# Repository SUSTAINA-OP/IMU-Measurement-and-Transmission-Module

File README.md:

<html lang="en">

<head>
    <meta charset="uft-8">
    <meta name="author" content="Masato Kubotera">
    <meta name="description" content="">
</head>

<body>
    <p><strong>This product is currently under development!</strong></p>
    <h1>IMU Measurement and Transmission Module</h1>
        <p>
            This product is a module enabling the <a href="https://github.com/SUSTAINA-OP/ICM-42688-P-Module">SUSTAINA-OP/ICM-42688-P-Module</a> (IMU module) to be connected to a USB or RS-485 I/F through a microcontroller.<br><br>
            The <a href="/firmware">firmware</a> for this product to be written to the microcontroller is a modification of the following library.
            <ul>
                <li><a href="https://github.com/finani/ICM42688">finani/ICM42688</a></li>
            </ul>
            (The firmware of this product currently supports only USB I/F connection.)
        </p>
    <h2>Features Rev. 1</h2>
        <p>
            <table>
                <tr>
                    <th>Top Surface of PCB</th>
                    <th>Bottom Surface of PCB</th>
                    <th>Assembled Electronic Components</th>
                </tr>
                <tr>
                    <td></td>
                    <td></td>
                    <td></td>
                </tr>
            </table>
        </p>
    <h3>PCB</h3>
        <p>
            <ul>
                <li>87mm x 25mm PCB layout</li>
            </ul>
        </p>
    <h2>Development Environments</h2>
    <p>
        This product is designed with the following software.
            <ul>
                <li><a href="https://www.autodesk.com/products/eagle/overview">Autodesk Eagle 9.6.2</a></li>
                <li><a href="https://www.arduino.cc/en/software">Arduino IDE 1.8.19</a></li>
            </ul>
    </p>
    <h2>Repository Contents</h2>
        <p>
            <dl>
                <dt><a href="/images">\images</a></dt>
                <dd>PCB preview images and capture of design screen</dd>
                <dt><a href="/libraries">\libraries</a></dt>
                <dd>Libraries used in Autodesk Eagle design</dd>
                <dt><a href="/pcb_order">\pcb_order</a> </dt>
                <dd>Gerber data and documentation for ordering PCB</dd>
                <dt><a href="/firmware">\firmware</a> </dt>
                <dd>Sample firmware to be written to the microcontroller board</dd>
                <dt><a href="/schematic.pdf">schematic.pdf</a></dt>
                <dd>Circuit diagram of this product</dd>
                <dt>*.brd</dt>
                <dd>Board wiring design file by Autodesk Eagle</dd>
                <dt>*.sch</dt>
                <dd>Circuit diagram design file by Autodesk Eagle</dd>
                <dt><a href="/.gitignore">.gitignore</a></dt>
                <dd>A file that tells Git not to track a particular file</dd>
                <dt><a href="/LICENSE">LICENSE</a></dt>
                <dd>License to use this product</dd>
            </dl>
        </p>
    <h2>Documentation</h2>
    <h3>Documentation</h3>
        <p>
            The following design errors have been identified in Rev. 1 of this product.
            <ul>
              <li>TXDEN of UART/RS-485 conversion IC is not wired to the microcontroller board</li>
                When used with USB I/F, there is no problem, but when used with RS-485 I/F, solder a jumper wire between TXDEN and the microcontroller as shown in the figure below.<br>
                
            </ul>
        </p>
    <h2>References</h2>
        
    <h2>Contact</h2>
        <p>
            If you have any questions, please contact the designer of this product, Masato Kubodera, by <a href="mailto:masato.kubotera@sustaina-op.com">e-mail</a>.<br>
            E-mail: <a href="mailto:masato.kubotera@sustaina-op.com">masato.kubotera@sustaina-op.com</a>
        </p>
    <h2>License Information</h2>
        <p>
            This product is open source. Please review the <a href="/LICENSE">LICENSE</a> for license information.<br>
            <br>
            This product by Masato Kubotera is licensed under a <a href="http://creativecommons.org/licenses/by-nc-sa/4.0/">Creative Commons Attribution-NonCommercial-ShareAlike 4.0 International License</a>.
        </p>
</body>
</html>

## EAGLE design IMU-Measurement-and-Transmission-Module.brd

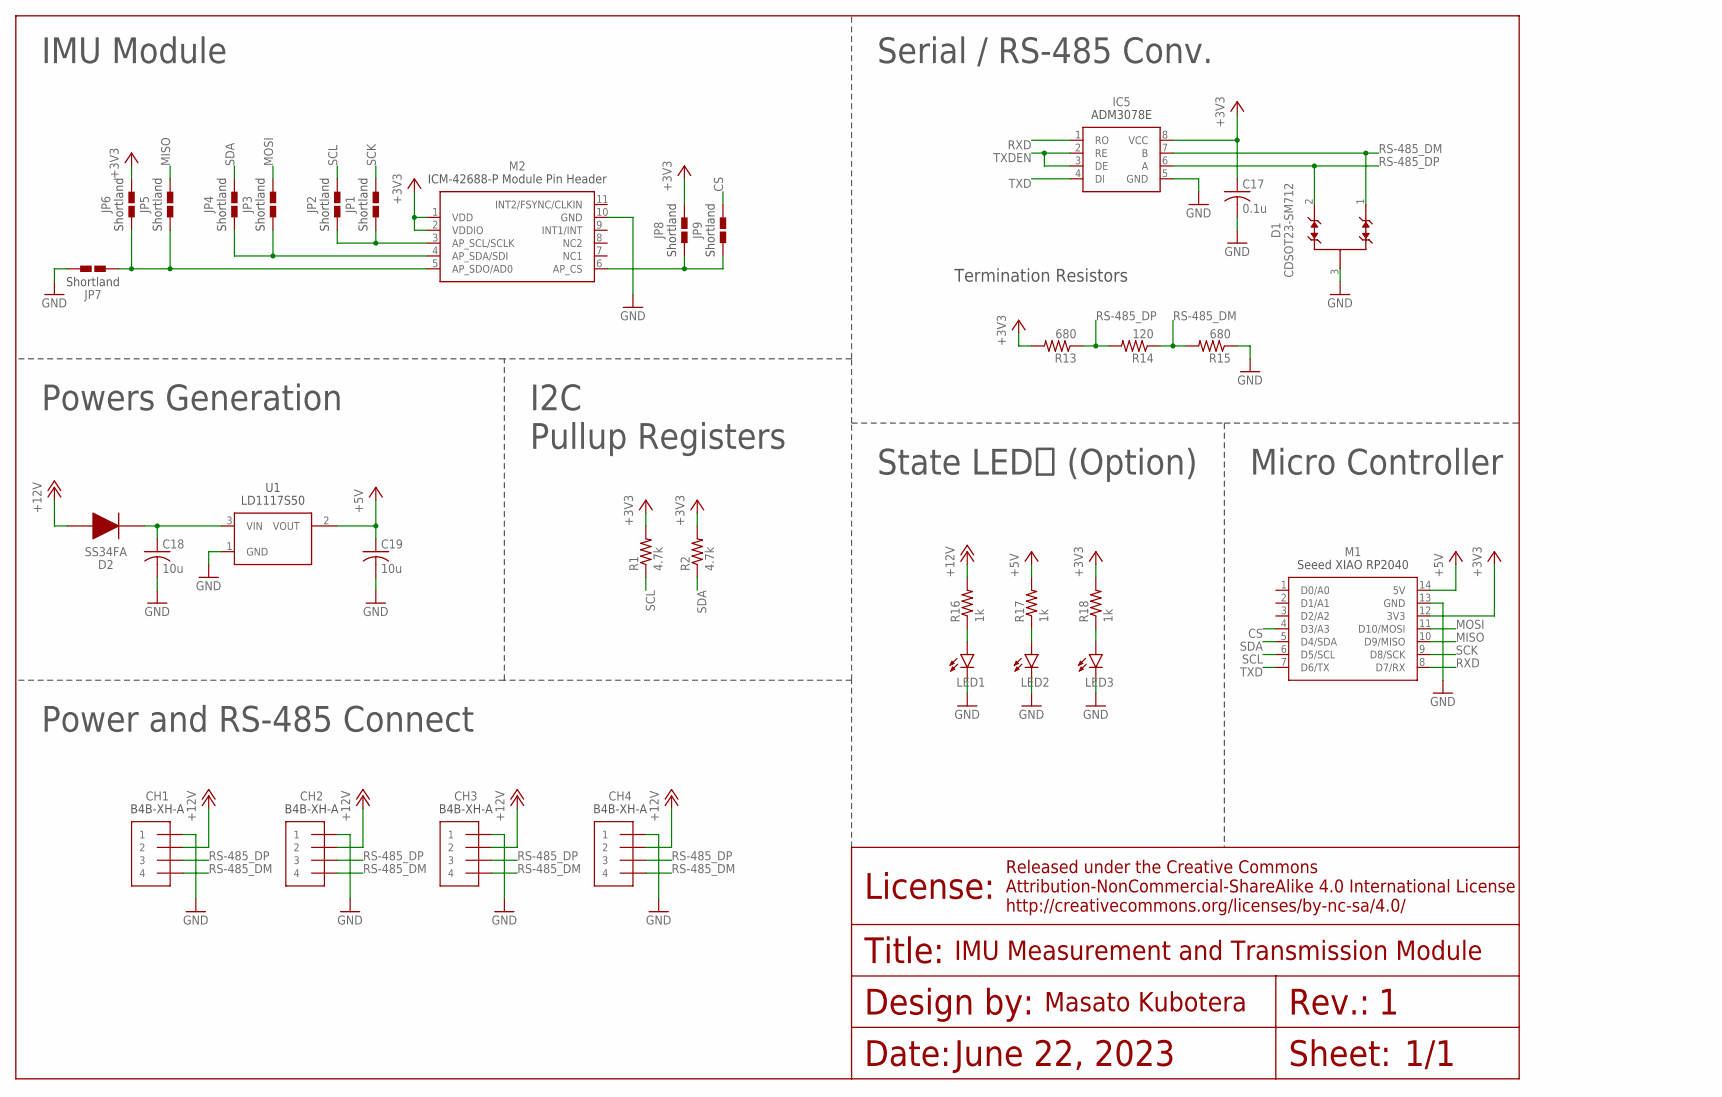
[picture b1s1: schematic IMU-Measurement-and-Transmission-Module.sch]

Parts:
C17: 0.1u; C0603
C18, C19: 10u; C0603
CH1, CH2, CH3, CH4: B4B-XH-A
D1: CDSOT23-SM712; SOT-23-3
D2: SS34FA
IC5: ADM3078E
JP1, JP2, JP3, JP4, JP5, JP6, JP7, JP8, JP9: SHORTLAND
LED1, LED2, LED3: LEDSML0603; SML0603
M1: SEEED_XIAO_RP2040_HOLE; SEEED_XIAO_HOLE
M2: ICM-42688-P-MODULE-PINHEADER
R1, R2: 4.7k; R0603
R13, R15: 680; R0603
R14: 120; R0603
R16, R17, R18: 1k; R0603
U1: LD1117S50; SOT-223

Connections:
3V3_LED: LED3.A, R18.1
5V_LED: LED2.A, R17.1
12V_LED: LED1.A, R16.1
+3V3: C17.1, IC5.8 (VCC), JP6.2, JP8.2, M1.12 (3V3), M2.1 (VDD), M2.2 (VDDIO), R1.2, R2.2, R13.2, R18.2
+5V: C19.1, M1.14 (5V), R17.2, U1.2 (VOUT)
+12V: CH1.2, CH2.2, CH3.2, CH4.2, D2.2, R16.2
AP_CS: JP8.1, JP9.1, M2.6 (AP_CS)
AP_SCL/SCLK: JP1.1, JP2.1, M2.3 (AP_SCL/SCLK)
AP_SDA/SDI: JP3.1, JP4.1, M2.4 (AP_SDA/SDI)
AP_SDO/ADO: JP5.1, JP6.1, JP7.1, M2.5 (AP_SDO/AD0)
CS: JP9.2, M1.4 (D3/A3)
GND: C17.2, C18.2, C19.2, CH1.1, CH2.1, CH3.1, CH4.1, D1.3, IC5.5 (GND), JP7.2, LED1.C, LED2.C, LED3.C, M1.13 (GND), M2.10 (GND), R15.1, U1.1 (GND)
MISO: JP5.2, M1.10 (D9/MISO)
MOSI: JP3.2, M1.11 (D10/MOSI)
RS-485_DM: CH1.4, CH2.4, CH3.4, CH4.4, D1.1, IC5.7 (B), R14.1, R15.2
RS-485_DP: CH1.3, CH2.3, CH3.3, CH4.3, D1.2, IC5.6 (A), R13.1, R14.2
RXD: IC5.1 (RO), M1.8 (D7/RX)
SCK: JP1.2, M1.9 (D8/SCK)
SCL: JP2.2, M1.6 (D5/SCL), R1.1
SDA: JP4.2, M1.5 (D4/SDA), R2.1
TXD: IC5.4 (DI), M1.7 (D6/TX)
TXDEN: IC5.2 (RE), IC5.3 (DE)
VIN: C18.1, D2.1, U1.3 (VIN)

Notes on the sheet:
Serial / RS-485 Conv.
Powers Generation
Micro Controller
State LEDｓ (Option)
Power and RS-485 Connect
1/1
June 22, 2023
IMU Measurement and Transmission Module
Termination Resistors
I2C Pullup Registers
IMU Module

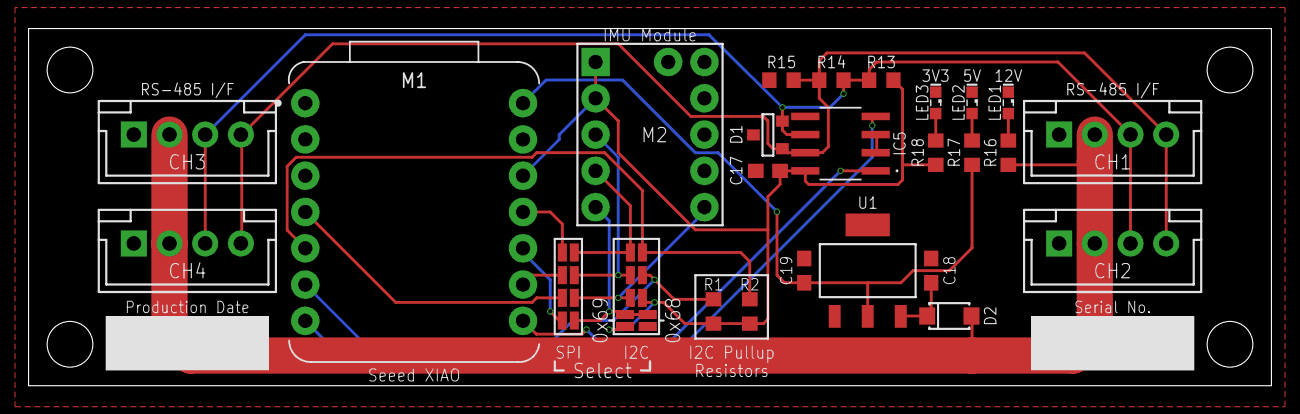
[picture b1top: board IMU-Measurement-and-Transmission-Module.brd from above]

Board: 2 copper layers, 87.0 x 25.0 mm, 33 parts (0 on the bottom side), 23 nets.

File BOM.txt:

Qty Value                        Device                       Package                      Parts                                       Description                
3                                LEDSML0603                   SML0603                      LED1, LED2, LED3                            LED                        
1   0.1u                         C-USC0603                    C0603                        C17                                         CAPACITOR, American symbol 
2   10u                          C-USC0603                    C0603                        C18, C19                                    CAPACITOR, American symbol 
1   120                          R-US_R0603                   R0603                        R14                                         RESISTOR, American symbol  
3   1k                           R-US_R0603                   R0603                        R16, R17, R18                               RESISTOR, American symbol  
2   4.7k                         R-US_R0603                   R0603                        R1, R2                                      RESISTOR, American symbol  
2   680                          R-US_R0603                   R0603                        R13, R15                                    RESISTOR, American symbol  
1   ADM3078E                     ADM3078E                     ADM3078E                     IC5                                                                    
4   B4B-XH-A                     B4B-XH-A                     B4B-XH-A                     CH1, CH2, CH3, CH4                                                     
1   CDSOT23-SM712                CDSOT23-SM712                SOT-23-3                     D1                                                                     
1   ICM-42688-P-MODULE-PINHEADER ICM-42688-P-MODULE-PINHEADER ICM-42688-P-MODULE-PINHEADER M2                                                                     
1   LD1117S50                    LD1117S50                    SOT-223                      U1                                                                     
1   SEEED_XIAO_RP2040_HOLE       SEEED_XIAO_RP2040_HOLE       SEEED_XIAO_HOLE              M1                                                                     
9   SHORTLAND                    SHORTLAND                    SHORTLAND                    JP1, JP2, JP3, JP4, JP5, JP6, JP7, JP8, JP9                            
1   SS34FA                       SS34FA                       SS34FA                       D2

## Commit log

2023-06-22 Initial upload
2023-06-29 Update pins of CS for SPI communication
2023-06-29 modified parameters for use with the SUSTAINA-OP
2023-07-04 Longer sleep time when writing settings
2023-07-04 Allowed the master cpu to perform the reset
2023-07-04 upload EAGLE files
2023-07-07 Changed the method of acquiring gyro bias to a method other than at the start
2023-07-08 Eliminate computerized resets from the master
2023-09-02 Added temperature (in degrees Celsius) to the measured value
2023-09-03 Added bias value and temperature acquisition by sending the letter T or t
2023-10-19 Remove unused variables
2023-11-06 moved the ICM42688 library hierarchy
2023-11-07 changed transmitted/received data to packet configuration
2023-11-08 added sample code for the master-slave side
2023-11-12 Changed to accept incoming data. Supports bias rewriting. Changed naming convention.
2023-11-12 Supports data transmission. Command options are supported, allowing the number of loops, commands, and data to be entered.
2023-11-12 Eliminated the reset command due to the fact that reconnecting the port resets it.
2023-11-12 Changed the method of sending byte data
2023-11-12 Removed unnecessary variable definitions
2023-11-12 Removed unneeded standard output
2023-11-12 Supports error detection related to IMU status
2023-11-14 Added libraries for mpu-9250
2023-11-16 Tentatively supports functions for MPU9250
2023-11-17 Changed to methods that do not rely on flash storage
2023-11-19 Addressed the problem that error handling related to WhoAmI takes one extra loop.
2023-11-19 Resolved syntax errors
2023-11-19 Changed the LED to light up when an error occurs.
2023-11-19 Changed baud rate setting function to a value-passing method
2023-11-19 Changed error name
2023-11-20 Added a note at the beginning
2023-11-20 Changed the display format of byte type variables

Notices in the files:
parts and their libraries:
Frames: Released under the Creative Commons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
